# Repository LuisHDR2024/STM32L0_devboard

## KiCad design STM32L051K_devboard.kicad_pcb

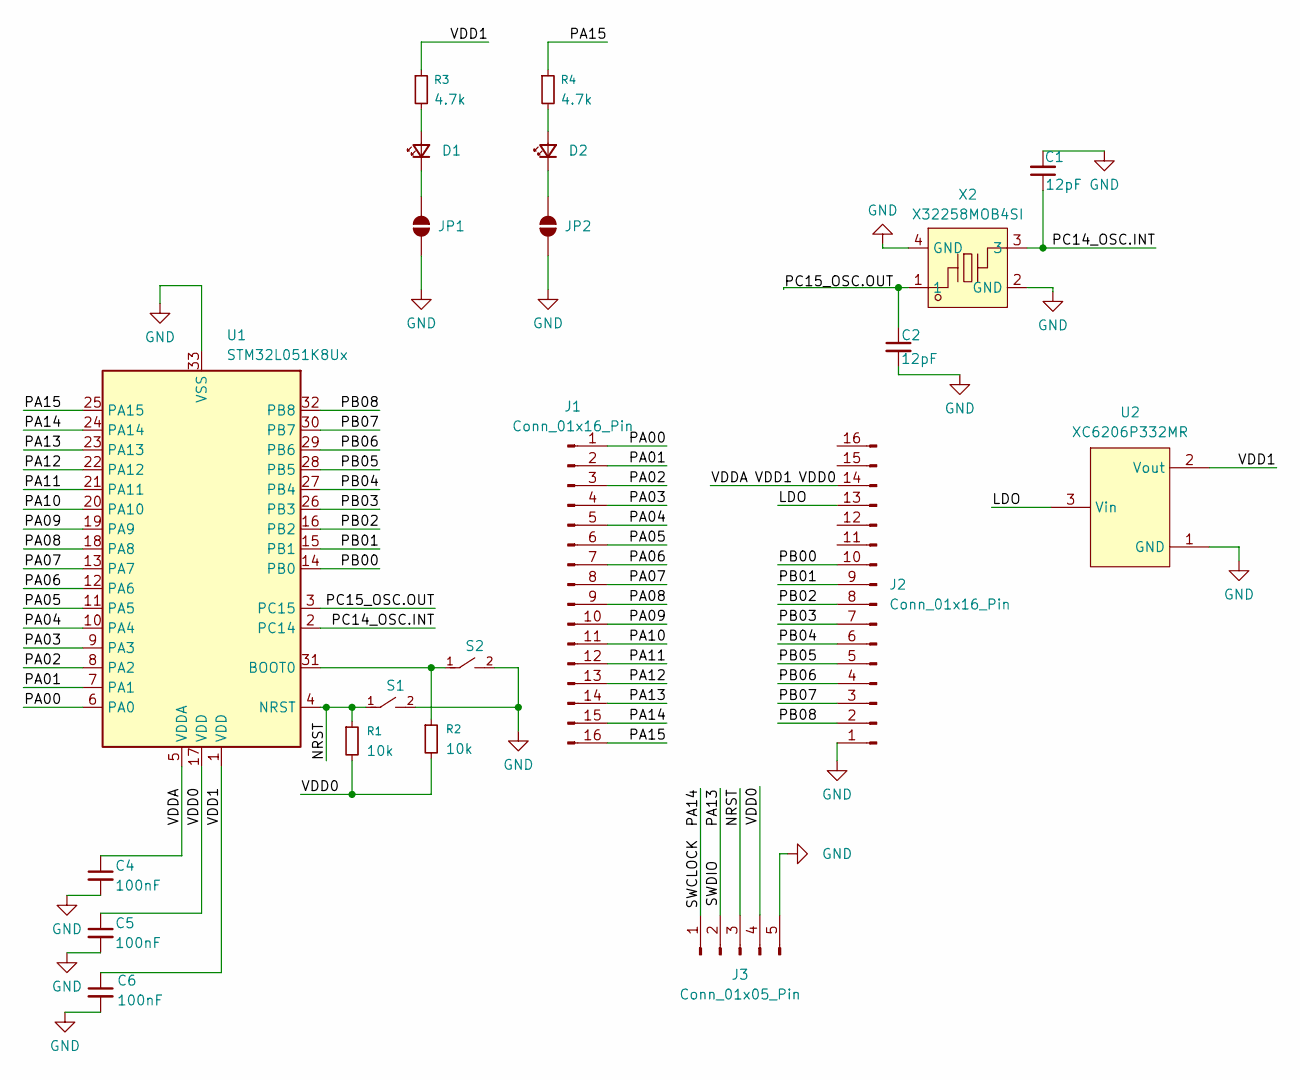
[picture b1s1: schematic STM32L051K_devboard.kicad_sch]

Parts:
C1, C2: 12pF; C_0603_1608Metric
C4, C5, C6: 100nF; C_0603_1608Metric
D1, D2: LED_Small; LED_0603_1608Metric
J1, J2: Conn_01x16_Pin; PinHeader_1x16_P2.54mm_Vertical
J3: Conn_01x05_Pin; PinHeader_1x05_P2.54mm_Vertical
JP1, JP2: SolderJumper_2_Open; SolderJumper-2_P1.3mm_Open_TrianglePad1.0x1.5mm
R1, R2: 10k; R_0603_1608Metric
R3, R4: 4.7k; R_0603_1608Metric
S1, S2: TS-1088-AR02016; SW_TS-1088-AR02016; PARTREV N/A
U1: STM32L051K8Ux; QFN-32-1EP_5x5mm_P0.5mm_EP3.45x3.45mm
U2: XC6206P332MR; SOT-23-3_L2.9-W1.6-P1.90-LS2.8-BR; MPN XC6206P332MR-G; LCSC Part C5446
X2: X32258MOB4SI; CRYSTAL-SMD_4P-L3.2-W2.5-BL; MPN X32258MOB4SI; LCSC Part C2682775

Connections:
/LDO: J2.13, U2.3 (Vin)
/NRST: J3.3, R1.1, S1.1, U1.4 (NRST)
/PA00: J1.1, U1.6 (PA0)
/PA01: J1.2, U1.7 (PA1)
/PA02: J1.3, U1.8 (PA2)
/PA03: J1.4, U1.9 (PA3)
/PA04: J1.5, U1.10 (PA4)
/PA05: J1.6, U1.11 (PA5)
/PA06: J1.7, U1.12 (PA6)
/PA07: J1.8, U1.13 (PA7)
/PA08: J1.9, U1.18 (PA8)
/PA09: J1.10, U1.19 (PA9)
/PA10: J1.11, U1.20 (PA10)
/PA11: J1.12, U1.21 (PA11)
/PA12: J1.13, U1.22 (PA12)
/PA13: J1.14, J3.2, U1.23 (PA13)
/PA14: J1.15, J3.1, U1.24 (PA14)
/PA15: J1.16, R4.1, U1.25 (PA15)
/PB00: J2.10, U1.14 (PB0)
/PB01: J2.9, U1.15 (PB1)
/PB02: J2.8, U1.16 (PB2)
/PB03: J2.7, U1.26 (PB3)
/PB04: J2.6, U1.27 (PB4)
/PB05: J2.5, U1.28 (PB5)
/PB06: J2.4, U1.29 (PB6)
/PB07: J2.3, U1.30 (PB7)
/PB08: J2.2, U1.32 (PB8)
/PC14_OSC.INT: C1.1, U1.2 (PC14), X2.3
/PC15_OSC.OUT: C2.1, U1.3 (PC15), X2.1
/VDD0: C4.1, C5.1, C6.1, J2.14, J3.4, R1.2, R2.2, R3.1, U1.1 (VDD), U1.5 (VDDA), U1.17 (VDD), U2.2 (Vout)
GND: C1.2, C2.2, C4.2, C5.2, C6.2, J2.1, J3.5, JP1.1 (A), JP2.1 (A), S1.2, S2.2, U1.33 (VSS), U2.1 (GND), X2.2 (GND), X2.4 (GND)
unnamed: D1.2 (A), R3.2
unnamed: D1.1 (K), JP1.2 (B)
unnamed: D2.2 (A), R4.2
unnamed: D2.1 (K), JP2.2 (B)
unnamed: R2.1, S2.1, U1.31 (BOOT0)

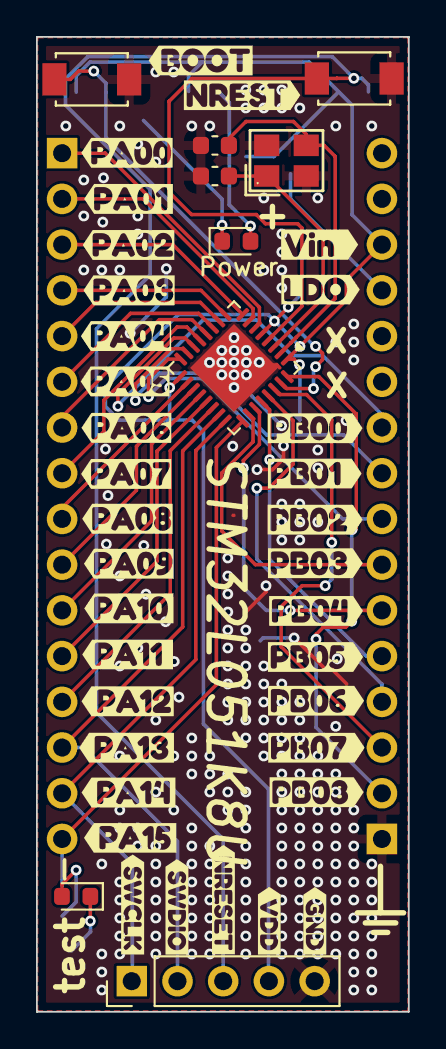
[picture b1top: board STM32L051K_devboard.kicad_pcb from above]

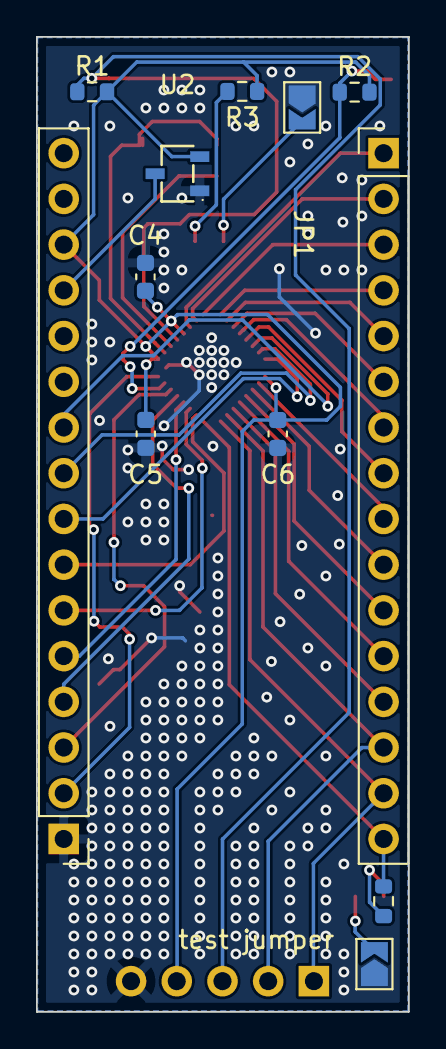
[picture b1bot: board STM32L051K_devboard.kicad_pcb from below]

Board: 4 copper layers, 20.7 x 54.2 mm, 55 parts (12 on the bottom side), 36 nets.

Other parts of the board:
kibuzzard-6A120E41: G***; kibuzzard-6A120E41
kibuzzard-6A0132A3: G***; kibuzzard-6A0132A3
kibuzzard-6A0132D3: G***; kibuzzard-6A0132D3
kibuzzard-6A0132E0: G***; kibuzzard-6A0132E0
kibuzzard-6A0132F9: G***; kibuzzard-6A0132F9
kibuzzard-6A0133A5: G***; kibuzzard-6A0133A5
kibuzzard-6A0133D4: G***; kibuzzard-6A0133D4
kibuzzard-6A0133F3: G***; kibuzzard-6A0133F3
kibuzzard-6A0134D7: G***; kibuzzard-6A0134D7
kibuzzard-6A0135B5: G***; kibuzzard-6A0135B5
kibuzzard-6A0135C4: G***; kibuzzard-6A0135C4
kibuzzard-6A0135ED: G***; kibuzzard-6A0135ED
kibuzzard-6A0135F3: G***; kibuzzard-6A0135F3
kibuzzard-6A389A11: G***; kibuzzard-6A389A11
kibuzzard-6A01330E: G***; kibuzzard-6A01330E
kibuzzard-6A01335E: G***; kibuzzard-6A01335E
kibuzzard-6A01346E: G***; kibuzzard-6A01346E
kibuzzard-6A01348C: G***; kibuzzard-6A01348C
kibuzzard-6A01353B: G***; kibuzzard-6A01353B
kibuzzard-6A01362E: G***; kibuzzard-6A01362E
kibuzzard-6A01363E: G***; kibuzzard-6A01363E
kibuzzard-6A013291: G***; kibuzzard-6A013291
kibuzzard-6A013338: G***; kibuzzard-6A013338
kibuzzard-6A013428: G***; kibuzzard-6A013428
kibuzzard-6A013453: G***; kibuzzard-6A013453
kibuzzard-6A013498: G***; kibuzzard-6A013498
kibuzzard-6A013521: G***; kibuzzard-6A013521
kibuzzard-6A013597: G***; kibuzzard-6A013597
kibuzzard-6A013611: G***; kibuzzard-6A013611
kibuzzard-69C453D6: G***; kibuzzard-69C453D6
kibuzzard-69C453E6: G***; kibuzzard-69C453E6
kibuzzard-69C453F2: G***; kibuzzard-69C453F2
kibuzzard-69C453FD: G***; kibuzzard-69C453FD
kibuzzard-69C45409: G***; kibuzzard-69C45409

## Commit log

2026-03-26 primer sabe
2026-03-30 cambios minimos
2026-05-16 Agregado XTAL low power y pines clock removidos
2026-05-23 agregado LDO y VDDA puenteado a 3.3
2026-06-21 cambio de crital a SMD 8 MHz
2026-06-29 agregado 4 capas y relleno
